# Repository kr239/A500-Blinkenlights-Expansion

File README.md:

# A500-Blinkenlights-Expansion

Blinkenlights diagnostics! 

Quasi useful diagnostic board - shows activity on the A500's expansion bus connector using LED's. May be useful for determining if certain signals aren't working on faulty boards. May also just look cool.

It's a 4-layer PCB though, due to the sheer number of signal traces, and also for neatness.

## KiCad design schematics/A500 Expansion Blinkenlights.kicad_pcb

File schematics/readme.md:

Drawn entirely in KiCad 5.1.2 - don't forget to grab the custom A500 Parts symbols and footprints.

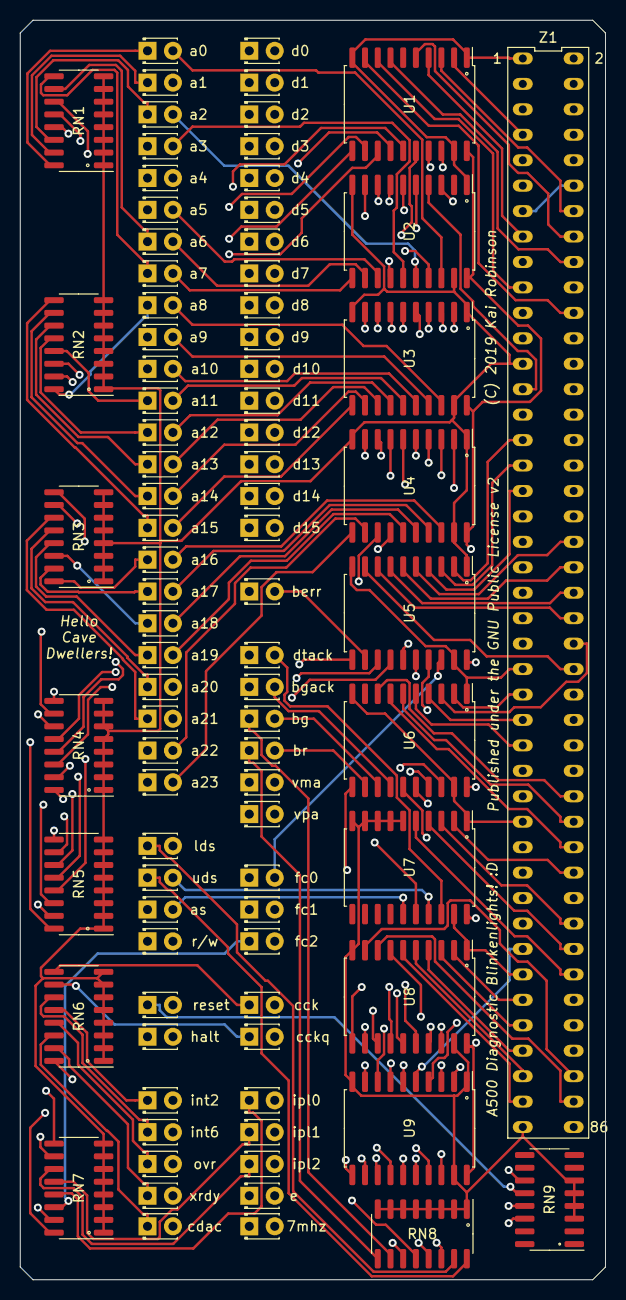
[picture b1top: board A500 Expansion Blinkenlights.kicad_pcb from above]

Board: 4 copper layers, 58.4 x 125.7 mm, 87 parts (0 on the bottom side), 204 nets.

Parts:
7mhz: LED_Small; LED_D1.8mm_W3.3mm_H2.4mm
RN1, RN2, RN3, RN4, RN5, RN6, RN7, RN8, RN9: R_Pack08; SOIC-16_3.9x9.9mm_P1.27mm
U1, U2, U3, U4, U5, U6, U7, U8, U9: 74LS541; SOIC-20W_7.5x12.8mm_P1.27mm
Z1: Zorro_Bus_Connector_2x43_A500
a0, a1, a2, a3, a4, a5, a6, a7, a8, a9, a10, a11, a12, a13, a14, a15, a16, a17, a18, a19, a20, a21, a22, a23: LED_Small; LED_D1.8mm_W3.3mm_H2.4mm
as: LED_Small; LED_D1.8mm_W3.3mm_H2.4mm
berr: LED_Small; LED_D1.8mm_W3.3mm_H2.4mm
bg: LED_Small; LED_D1.8mm_W3.3mm_H2.4mm
bgack: LED_Small; LED_D1.8mm_W3.3mm_H2.4mm
br: LED_Small; LED_D1.8mm_W3.3mm_H2.4mm
cck: LED_Small; LED_D1.8mm_W3.3mm_H2.4mm
cckq: LED_Small; LED_D1.8mm_W3.3mm_H2.4mm
cdac: LED_Small; LED_D1.8mm_W3.3mm_H2.4mm
d0, d1, d2, d3, d4, d5, d6, d7, d8, d9, d10, d11, d12, d13, d14, d15: LED_Small; LED_D1.8mm_W3.3mm_H2.4mm
dtack: LED_Small; LED_D1.8mm_W3.3mm_H2.4mm
e: LED_Small; LED_D1.8mm_W3.3mm_H2.4mm
fc0, fc1, fc2: LED_Small; LED_D1.8mm_W3.3mm_H2.4mm
halt: LED_Small; LED_D1.8mm_W3.3mm_H2.4mm
int2, int6: LED_Small; LED_D1.8mm_W3.3mm_H2.4mm
ipl0, ipl1, ipl2: LED_Small; LED_D1.8mm_W3.3mm_H2.4mm
lds: LED_Small; LED_D1.8mm_W3.3mm_H2.4mm
ovr: LED_Small; LED_D1.8mm_W3.3mm_H2.4mm
r/w: LED_Small; LED_D1.8mm_W3.3mm_H2.4mm
reset: LED_Small; LED_D1.8mm_W3.3mm_H2.4mm
uds: LED_Small; LED_D1.8mm_W3.3mm_H2.4mm
vma: LED_Small; LED_D1.8mm_W3.3mm_H2.4mm
vpa: LED_Small; LED_D1.8mm_W3.3mm_H2.4mm
xrdy: LED_Small; LED_D1.8mm_W3.3mm_H2.4mm

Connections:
/7mhz_in: U1.2, Z1.7
/7mhz_out: 7mhz.2, U1.18
/GND: RN1.1, RN1.2, RN1.3, RN1.4, RN1.5, RN1.6, RN1.7, RN1.8, RN2.1, RN2.2, RN2.3, RN2.4, RN2.5, RN2.6, RN2.7, RN2.8, RN3.1, RN3.2, RN3.3, RN3.4, RN3.5, RN3.6, RN3.7, RN3.8, RN4.1, RN4.2, RN4.3, RN4.4, RN4.5, RN4.6, RN4.7, RN4.8, RN5.1, RN5.2, RN5.3, RN5.4, RN5.5, RN5.6, RN5.7, RN5.8, RN6.1, RN6.2, RN6.3, RN6.4, RN6.5, RN6.6, RN6.7, RN6.8, RN7.1, RN7.2, RN7.3, RN7.4, RN7.5, RN7.6, RN7.7, RN7.8, RN8.1, RN8.2, RN8.3, RN8.4, RN8.5, RN8.6, RN8.7, RN8.8, RN9.3, RN9.4, RN9.5, RN9.6, U1.1, U1.10, U1.19, U2.1, U2.10, U2.19, U3.1, U3.10, U3.19, U4.1, U4.10, U4.19, U5.1, U5.10, U5.19, U6.1, U6.10, U6.19, U7.1, U7.6, U7.7, U7.8, U7.9, U7.10, U7.19, U8.1, U8.10, U8.19, U9.1, U9.10, U9.19, Z1.1, Z1.2, Z1.3, Z1.4, Z1.12, Z1.13, Z1.25, Z1.37, Z1.49, Z1.61, Z1.73, Z1.85
/VCC: Z1.5, Z1.6
/VCC5: U1.20, U2.20, U3.20, U4.20, U5.20, U6.20, U7.20, U8.20, U9.20
/_as_in: U7.5, Z1.74
/_as_out: U7.15, as.2
/_bg_in: U6.7, Z1.64
/_bg_out: U6.13, bg.2
/_bgack_in: U6.6, Z1.62
/_bgack_out: U6.14, bgack.2
/_br_in: U6.8, Z1.60
/_br_out: U6.12, br.2
/_cck_in: U1.4, Z1.15
/_cck_out: U1.16, cck.2
/_cckq_in: U1.3, Z1.14
/_cckq_out: U1.17, cckq.2
/_dtack_in: U7.2, Z1.66
/_dtack_out: U7.18, dtack.2
/_int2_in: U1.8, Z1.19
/_int2_out: U1.12, int2.2
/_int6_in: U1.9, Z1.22
/_int6_out: U1.11, int6.2
/_ipl0_in: U5.5, Z1.40
/_ipl0_out: U5.15, ipl0.2
/_ipl1_in: U5.6, Z1.42
/_ipl1_out: U5.14, ipl1.2
/_ipl2_in: U5.7, Z1.44
/_ipl2_out: U5.13, ipl2.2
/_lds_in: U7.4, Z1.72
/_lds_out: U7.16, lds.2
/_ovr_in: U1.7, Z1.18
/_ovr_out: U1.13, ovr.2
/_rw_out: U6.11, r/w.2
/_uds_in: U7.3, Z1.70
/_uds_out: U7.17, uds.2
/a0_out: U2.18, a0.2
/a1_in: U2.3, Z1.29
/a1_out: U2.17, a1.2
/a2_in: U2.4, Z1.27
/a2_out: U2.16, a2.2
/a3_in: U2.5, Z1.26
/a3_out: U2.15, a3.2
/a4_in: U2.6, Z1.24
/a4_out: U2.14, a4.2
/a5_in: U2.7, Z1.21
/a5_out: U2.13, a5.2
/a6_in: U2.8, Z1.23
/a6_out: U2.12, a6.2
/a7_in: U2.9, Z1.28
/a7_out: U2.11, a7.2
/a8_in: U3.2, Z1.30
/a8_out: U3.18, a8.2
/a9_in: U3.3, Z1.32
/a9_out: U3.17, a9.2
/a10_in: U3.4, Z1.34
/a10_out: U3.16, a10.2
/a11_in: U3.5, Z1.36
/a11_out: U3.15, a11.2
/a12_in: U3.6, Z1.38
/a12_out: U3.14, a12.2
/a13_in: U3.7, Z1.39
/a13_out: U3.13, a13.2
/a14_in: U3.8, Z1.41
/a14_out: U3.12, a14.2
/a15_in: U3.9, Z1.43
/a15_out: U3.11, a15.2
/a16_in: U4.2, Z1.45
/a16_out: U4.18, a16.2
/a17_in: U4.3, Z1.47
/a17_out: U4.17, a17.2
/a18_in: U4.4, Z1.52
/a18_out: U4.16, a18.2
/a19_in: U4.5, Z1.54
/a19_out: U4.15, a19.2
/a20_in: U4.6, Z1.56
/a20_out: U4.14, a20.2
/a21_in: U4.7, Z1.57
/a21_out: U4.13, a21.2
/a22_in: U4.8, Z1.58
/a22_out: U4.12, a22.2
/a23_in: U4.9, Z1.59
/a23_out: U4.11, a23.2
/berr_in: U5.8, Z1.46
/berr_out: U5.12, berr.2
/cdac_out: U1.14, cdac.2
/d0_in: U8.2, Z1.75
/d0_out: U8.18, d0.2
/d1_in: U8.3, Z1.77
/d1_out: U8.17, d1.2
/d2_in: U8.4, Z1.79
/d2_out: U8.16, d2.2
/d3_in: U8.5, Z1.81
/d3_out: U8.15, d3.2
/d4_in: U8.6, Z1.83
/d4_out: U8.14, d4.2
/d5_in: U8.7, Z1.86
/d5_out: U8.13, d5.2
/d6_in: U8.8, Z1.84
/d6_out: U8.12, d6.2
/d7_in: U8.9, Z1.82
/d7_out: U8.11, d7.2
/d8_in: U9.2, Z1.80
/d8_out: U9.18, d8.2
/d9_in: U9.3, Z1.78
/d9_out: U9.17, d9.2
/d10_in: U9.4, Z1.76
/d10_out: U9.16, d10.2
/d11_in: U9.5, Z1.71
/d11_out: U9.15, d11.2
/d12_in: U9.6, Z1.69
/d12_out: U9.14, d12.2
/d13_in: U9.7, Z1.67
/d13_out: U9.13, d13.2
/d14_in: U9.8, Z1.65
/d14_out: U9.12, d14.2
/d15_in: U9.9, Z1.63
/d15_out: U9.11, d15.2
/e_in: U5.9, Z1.50
/e_out: U5.11, e.2
/fc0_in: U5.2, Z1.31
/fc0_out: U5.18, fc0.2
/fc1_in: U5.3, Z1.33
/fc1_out: U5.17, fc1.2
/fc2_in: U5.4, Z1.35
/fc2_out: U5.16, fc2.2
/halt_in: U6.5, Z1.55
/halt_out: U6.15, halt.2
/reset_in: U6.4, Z1.53
/reset_out: U6.16, reset.2
/vma_in: U6.2, Z1.51
/vma_out: U6.18, vma.2
/vpa_in: U6.3, Z1.48
/vpa_out: U6.17, vpa.2
/xrdy_in: U1.5, Z1.16
/xrdy_out: U1.15, xrdy.2
unnamed: 7mhz.1, RN6.16
unnamed: RN1.9, a7.1
unnamed: RN1.10, a6.1
unnamed: RN1.11, a5.1
unnamed: RN1.12, a4.1
unnamed: RN1.13, a3.1
unnamed: RN1.14, a2.1
unnamed: RN1.15, a1.1
unnamed: RN1.16, a0.1
unnamed: RN2.9, a15.1
unnamed: RN2.10, a14.1
unnamed: RN2.11, a13.1
unnamed: RN2.12, a12.1
unnamed: RN2.13, a11.1
unnamed: RN2.14, a10.1
unnamed: RN2.15, a9.1
unnamed: RN2.16, a8.1
unnamed: RN3.9, a23.1
unnamed: RN3.10, a22.1
unnamed: RN3.11, a21.1
unnamed: RN3.12, a20.1
unnamed: RN3.13, a19.1
unnamed: RN3.14, a18.1
unnamed: RN3.15, a17.1
unnamed: RN3.16, a16.1
unnamed: RN4.9, d7.1
unnamed: RN4.10, d6.1
unnamed: RN4.11, d5.1
unnamed: RN4.12, d4.1
unnamed: RN4.13, d3.1
unnamed: RN4.14, d2.1
unnamed: RN4.15, d1.1
unnamed: RN4.16, d0.1
unnamed: RN5.9, d15.1
unnamed: RN5.10, d14.1
unnamed: RN5.11, d13.1
unnamed: RN5.12, d12.1
unnamed: RN5.13, d11.1
unnamed: RN5.14, d10.1
unnamed: RN5.15, d9.1
unnamed: RN5.16, d8.1
unnamed: RN6.9, cck.1
unnamed: RN6.10, cckq.1
unnamed: RN6.11, int6.1
unnamed: RN6.12, int2.1
unnamed: RN6.13, ovr.1
unnamed: RN6.14, cdac.1
unnamed: RN6.15, xrdy.1
unnamed: RN7.9, dtack.1
unnamed: RN7.10, bgack.1
unnamed: RN7.11, ipl2.1
unnamed: RN7.12, ipl1.1
unnamed: RN7.13, ipl0.1
unnamed: RN7.14, fc2.1
unnamed: RN7.15, fc1.1
unnamed: RN7.16, fc0.1
unnamed: RN8.9, br.1
unnamed: RN8.10, bg.1
unnamed: RN8.11, e.1
unnamed: RN8.12, berr.1
unnamed: RN8.13, r/w.1
unnamed: RN8.14, as.1
unnamed: RN8.15, lds.1
unnamed: RN8.16, uds.1
unnamed: RN9.11, halt.1
unnamed: RN9.12, reset.1
unnamed: RN9.13, vpa.1
unnamed: RN9.14, vma.1

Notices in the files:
schematics/A500 Expansion Blinkenlights.kicad_pcb:
(C) 2019 Kai Robinson
Published under the GNU Public License v2
